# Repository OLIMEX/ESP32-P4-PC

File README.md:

# ESP32-P4-PC
ESP32-P4 all in one computer with x4 USB hosts Audio, HDMI, MIPI CSI, MIPI DSI, LiPo battery operation, Ethernet with POE

https://www.olimex.com/Products/IoT/ESP32-P4/ESP32-P4-PC/open-source-hardware

## Licensee
* Hardware is released under CERN Open Hardware Licence Version 2 - Strongly Reciprocal
* Software is released under MIT Licensee
* Documentation is released under CC BY-SA 4.0

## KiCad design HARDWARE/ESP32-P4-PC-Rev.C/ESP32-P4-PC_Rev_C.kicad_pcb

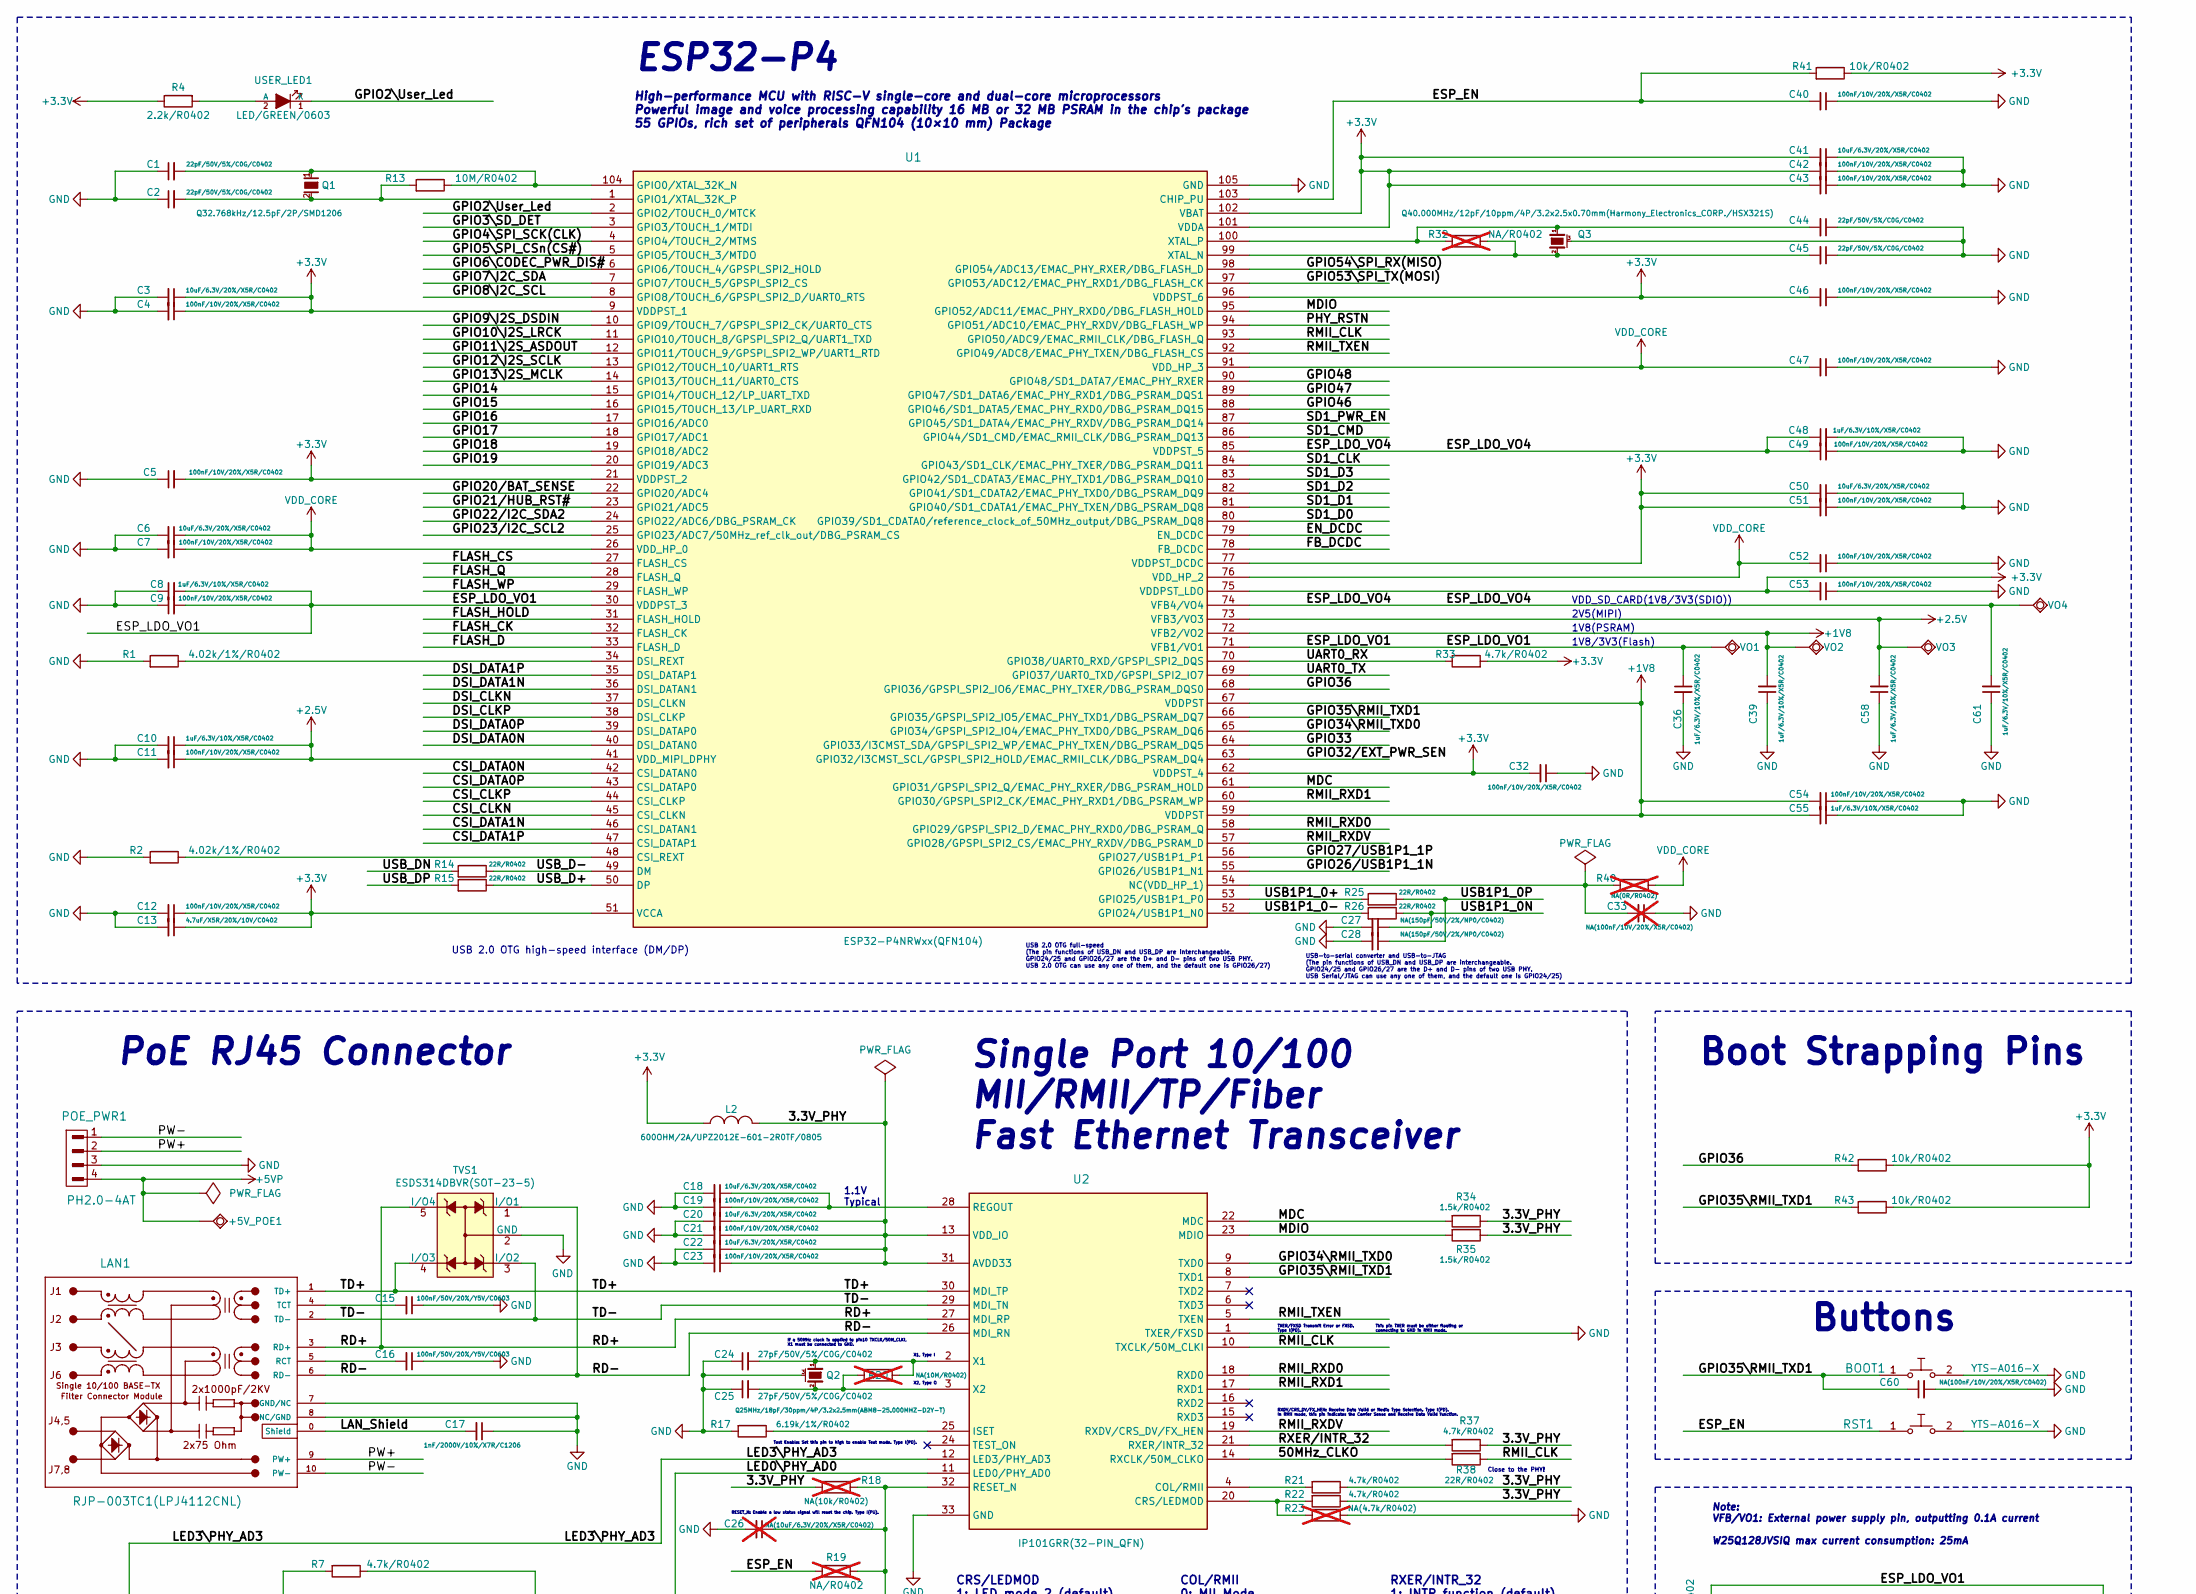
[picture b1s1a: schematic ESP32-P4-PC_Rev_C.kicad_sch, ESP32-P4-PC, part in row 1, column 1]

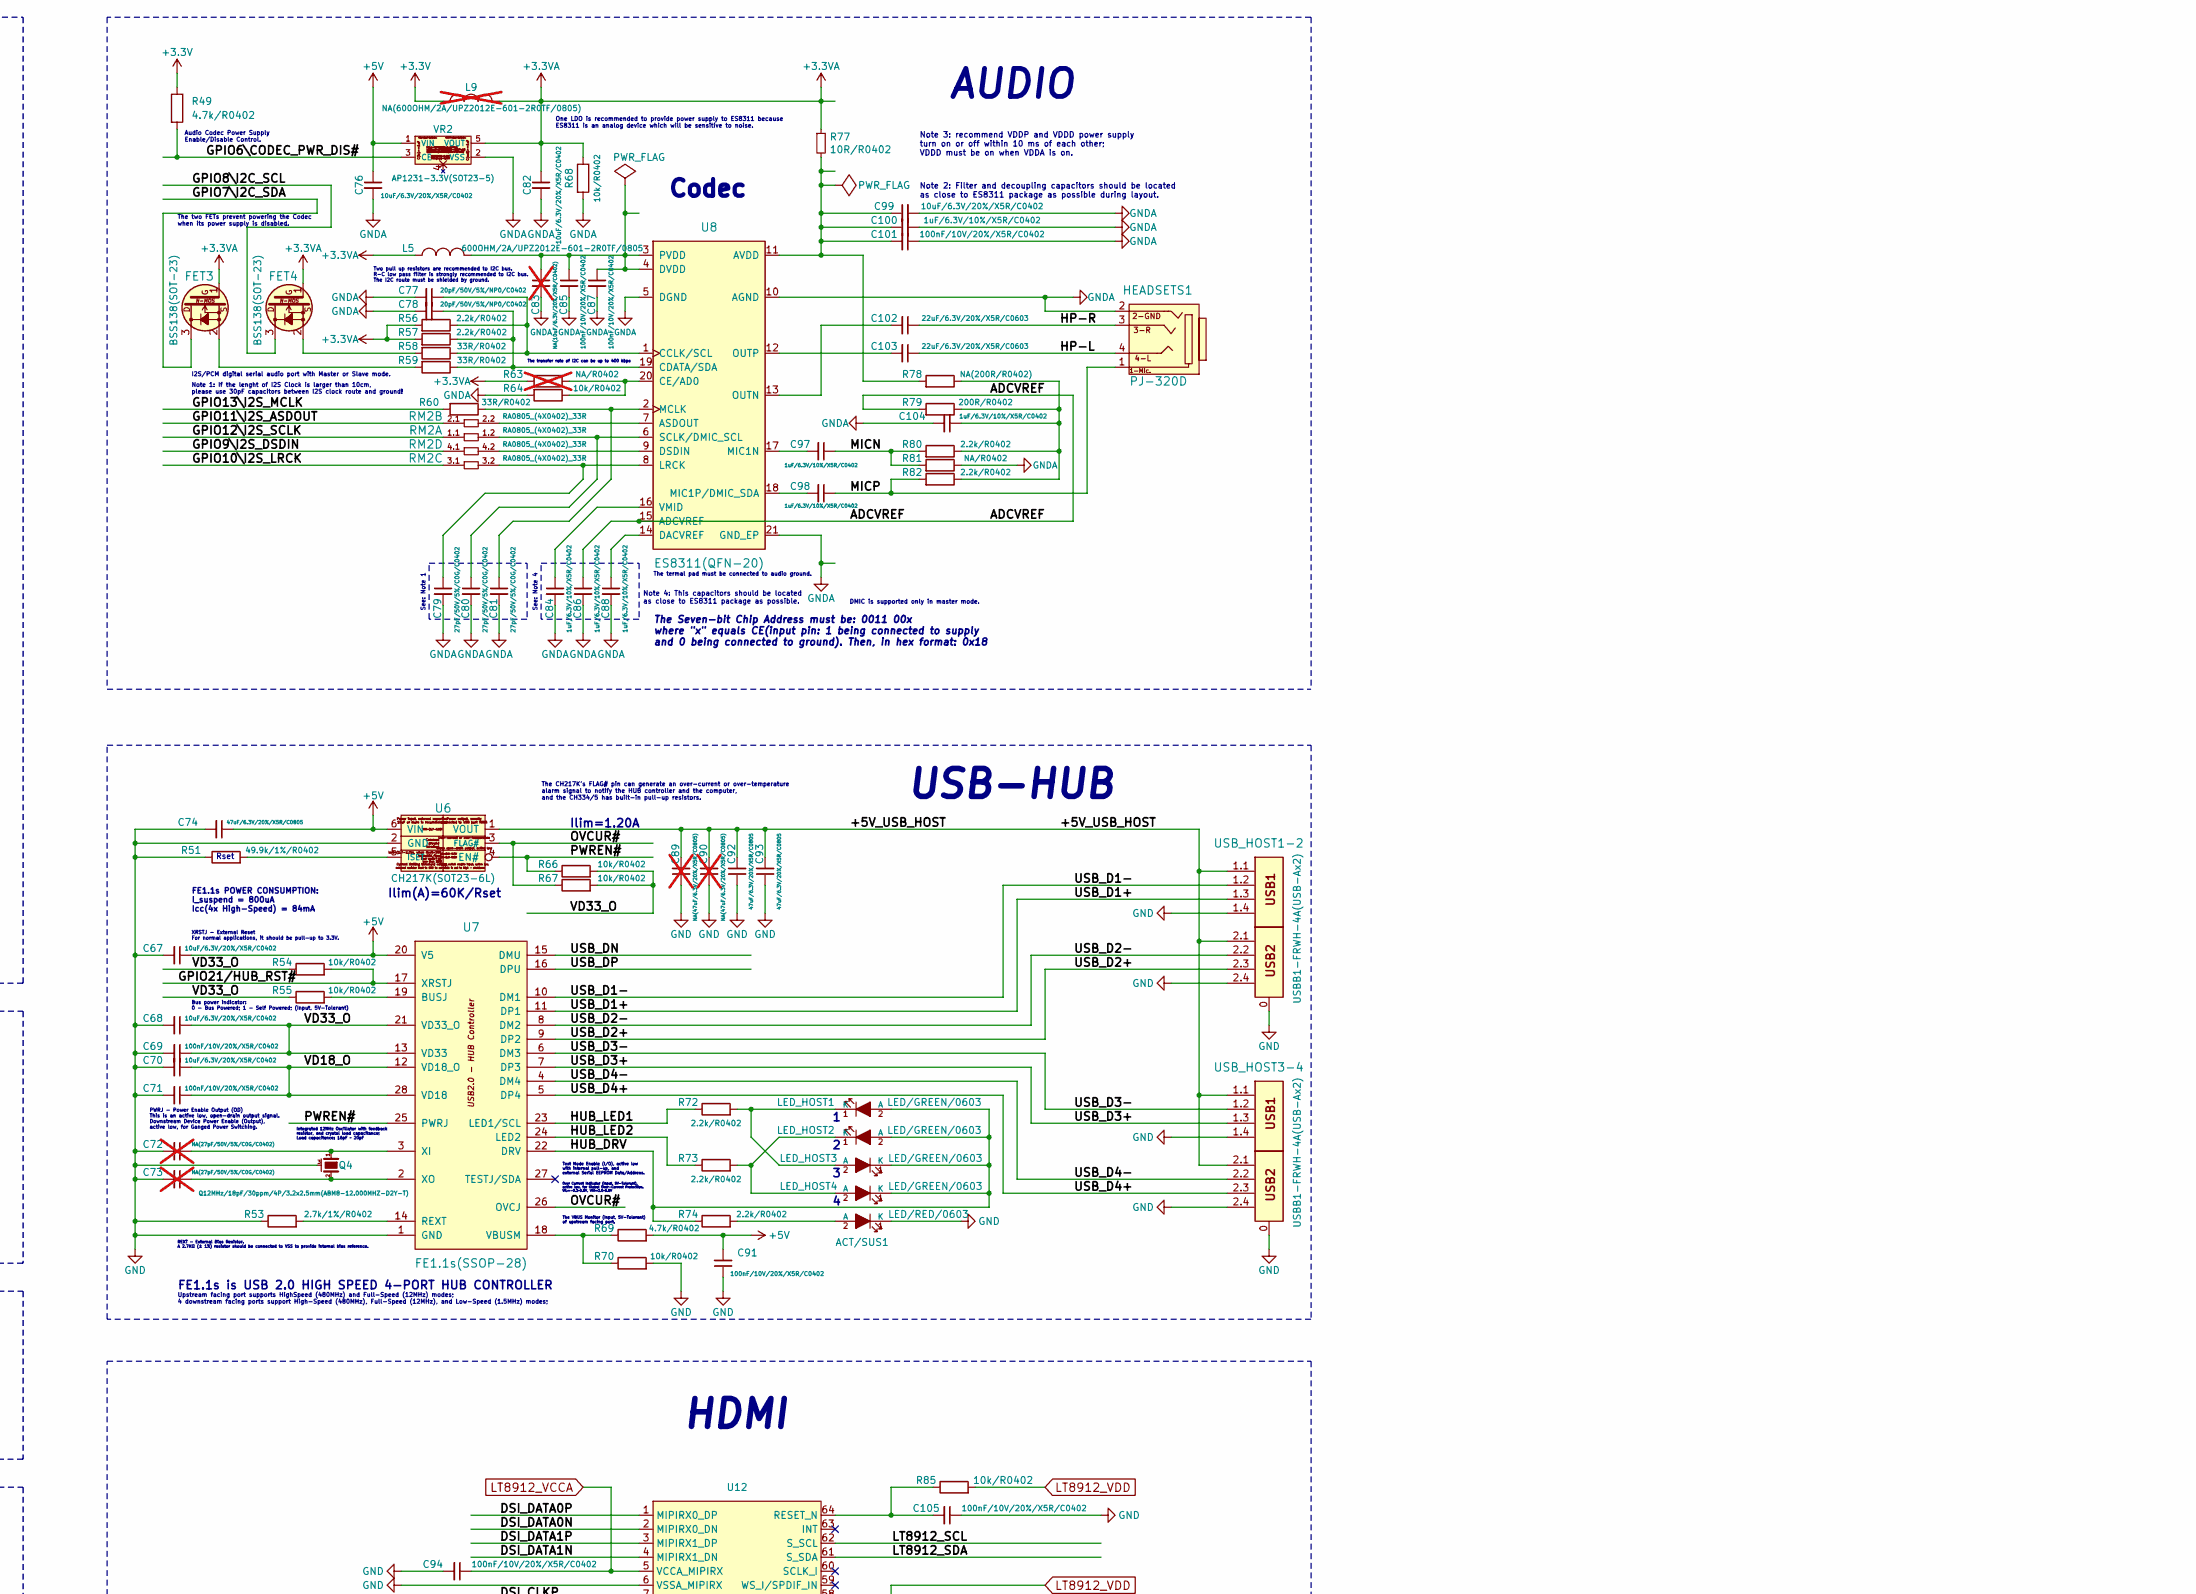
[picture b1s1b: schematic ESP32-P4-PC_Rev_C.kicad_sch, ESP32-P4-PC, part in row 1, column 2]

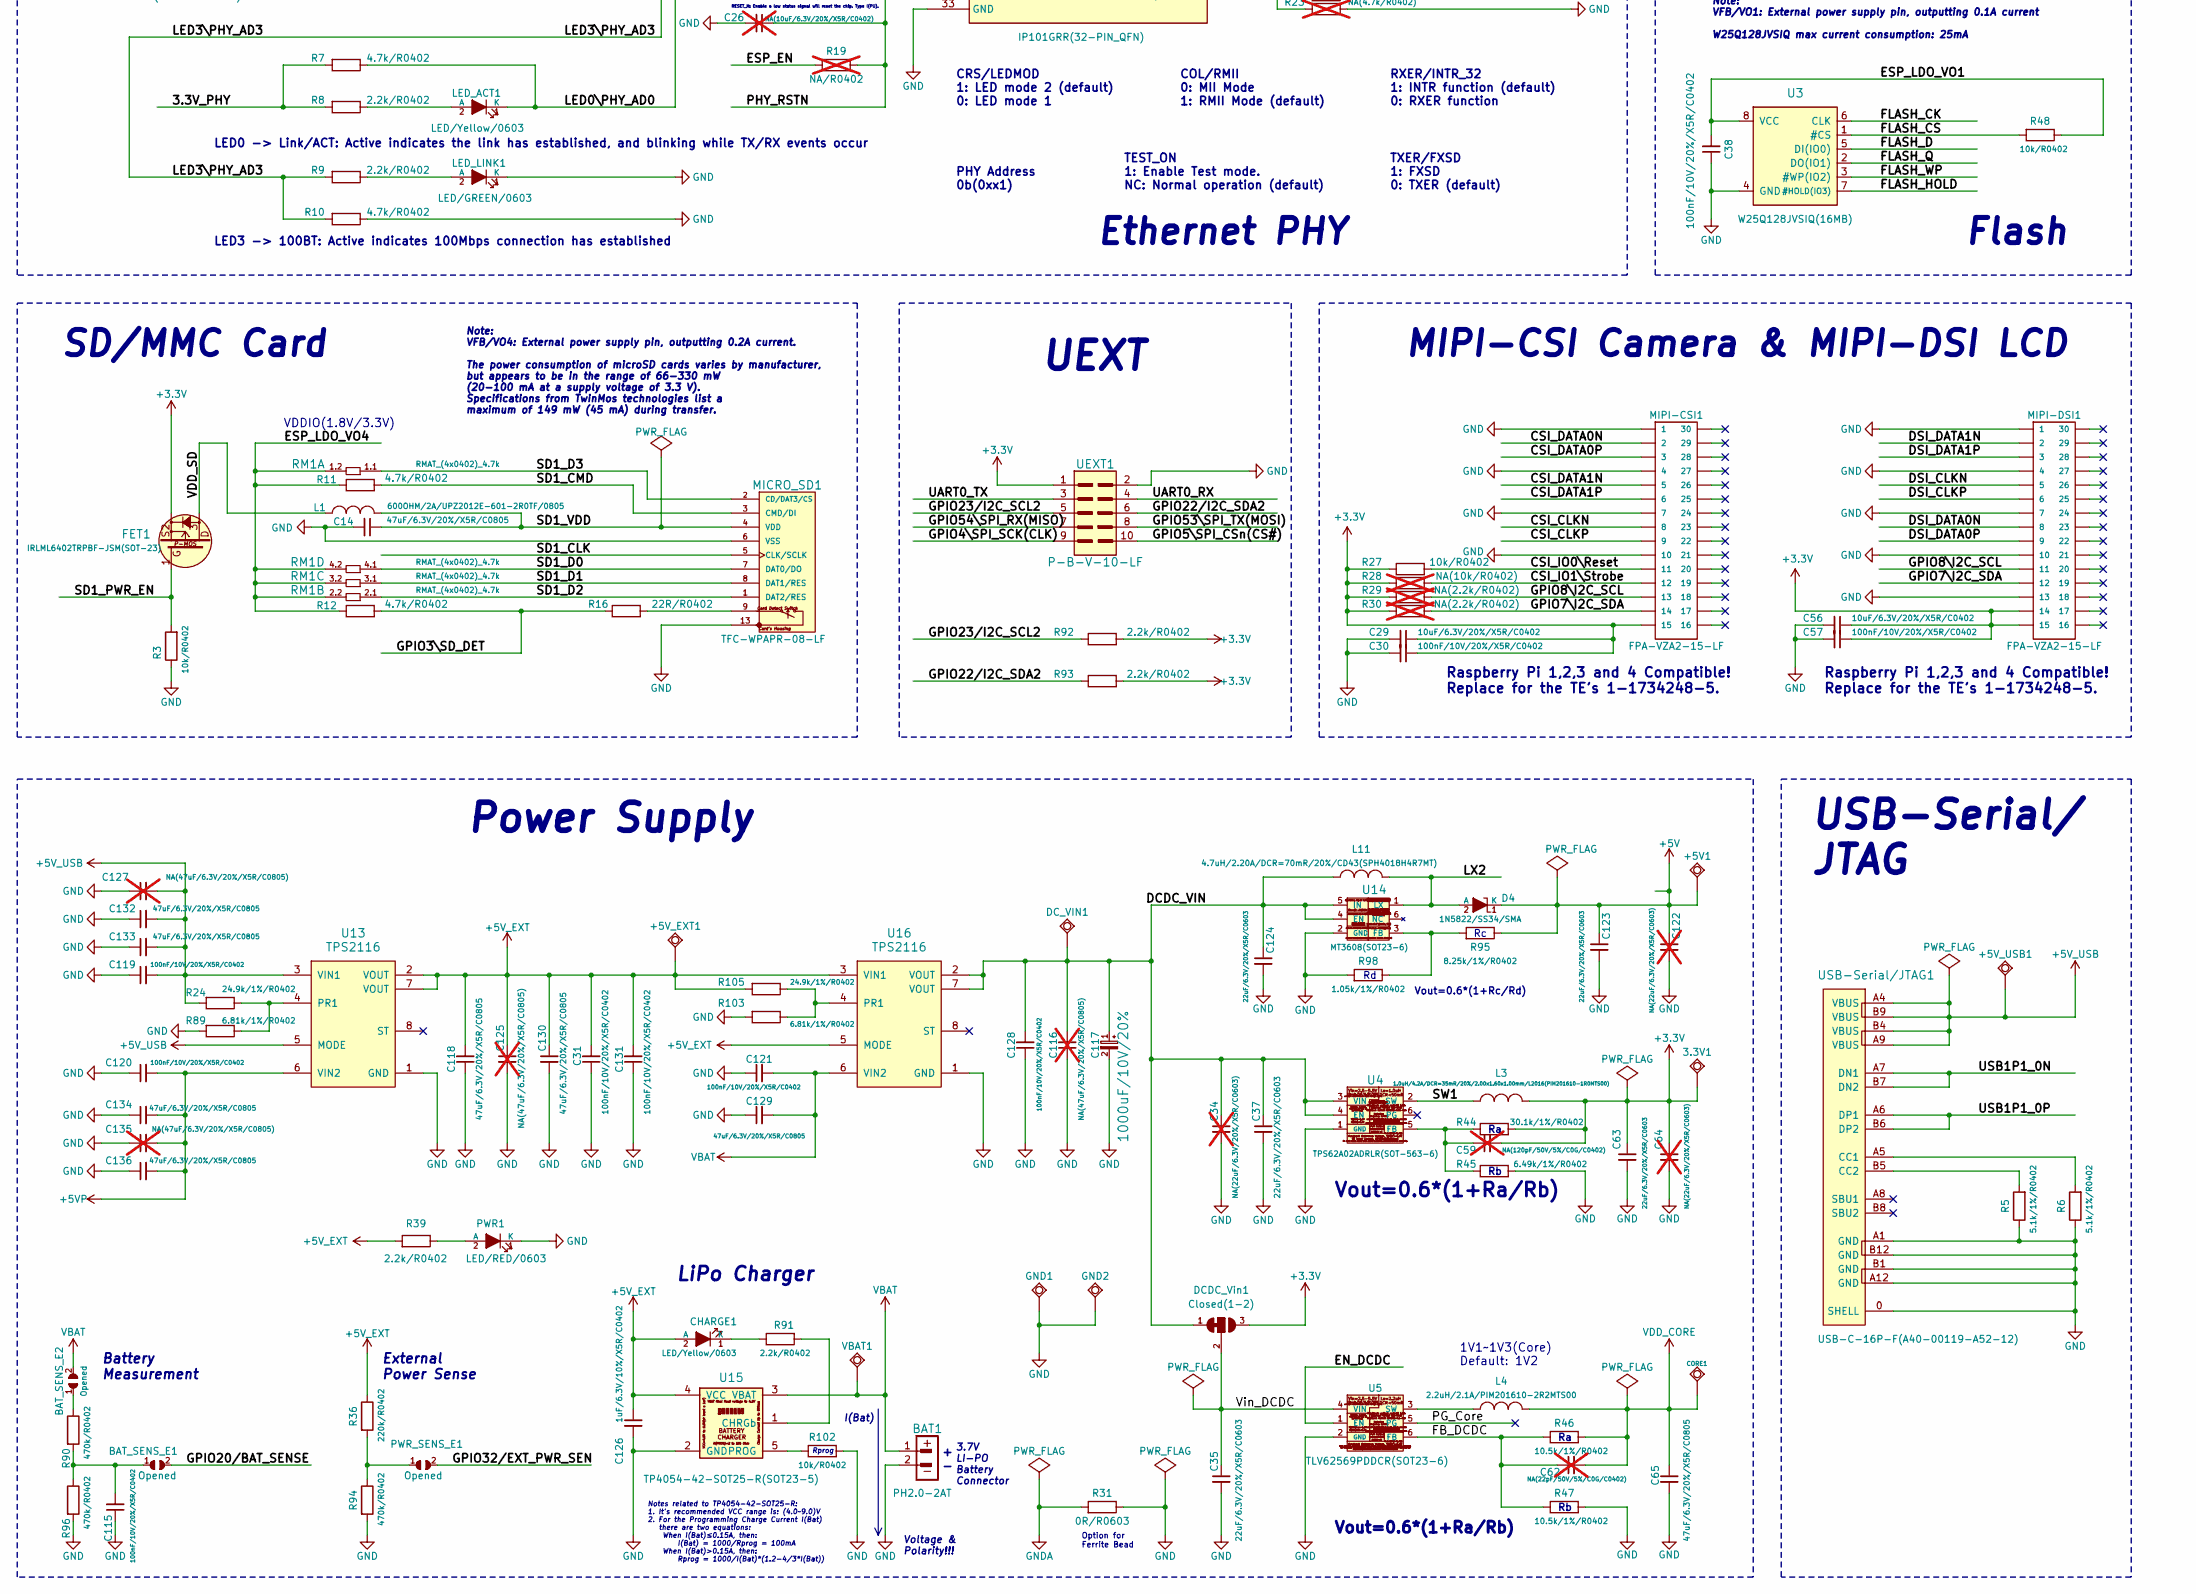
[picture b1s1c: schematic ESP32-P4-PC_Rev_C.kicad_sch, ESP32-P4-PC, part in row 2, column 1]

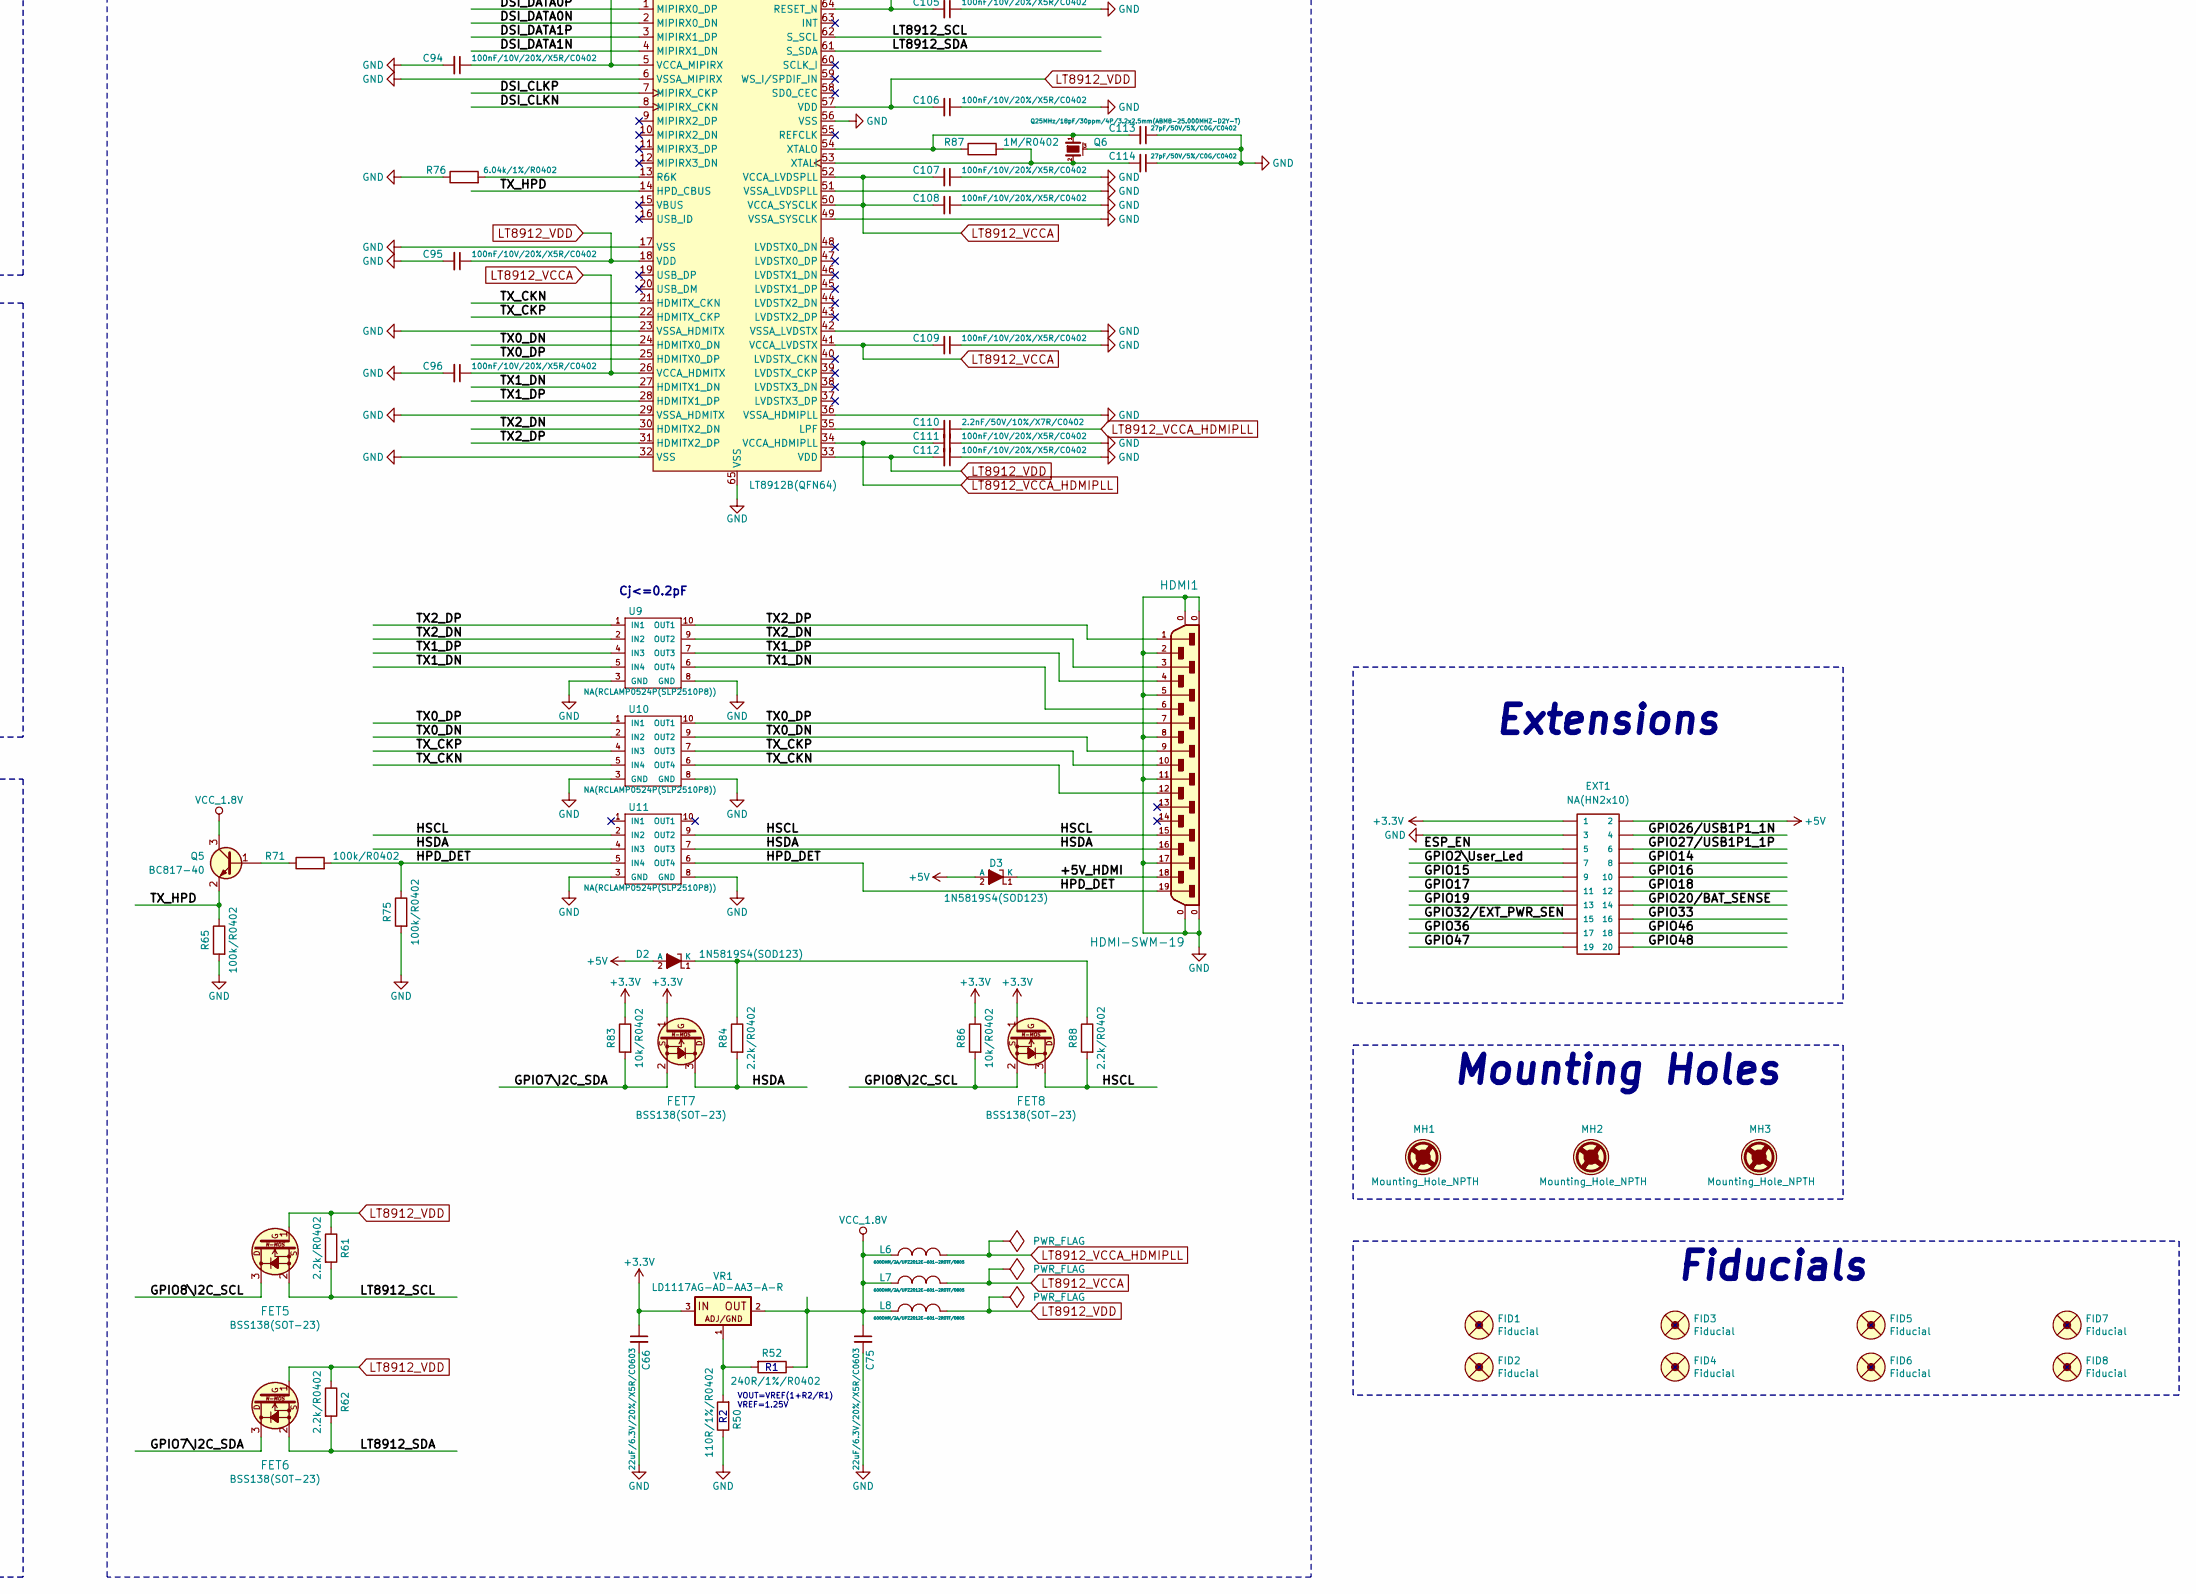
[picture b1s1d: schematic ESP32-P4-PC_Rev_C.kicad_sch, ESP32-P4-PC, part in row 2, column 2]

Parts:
3.3V1: TESTPAD; TESTPAD_40-ROUND
+5V1, +5V_EXT1, +5V_POE1, +5V_USB1: TESTPAD; TESTPAD_40-ROUND
ACT/SUS1: LED/RED/0603; LED_0603_KA
BAT1: PH2.0-2AT; PH2.0-2AT(BAT)
BAT_SENS_E1, BAT_SENS_E2: Opened; SJ_1_SMALLER
BOOT1: YTS-A016-X
C1, C2, C44, C45: 22pF/50V/5%/C0G/C0402; C_0402_5MIL_DWS
C3, C6, C18, C20, C22, C29, C41, C50, C56, C67, C68, C70, C76, C82, C99: 10uF/6.3V/20%/X5R/C0402; C_0402_5MIL_DWS
C4, C5, C7, C9, C11, C12, C19, C21, C23, C30, C31, C32, C38, C40, C42, C43, C46, C47, C49, C51, C52, C53, C54, C57, C69, C71, C85, C87, C91, C94, C95, C96, C101, C105, C106, C107, C108, C109, C111, C112, C115, C119, C120, C121, C128, C131: 100nF/10V/20%/X5R/C0402; C_0402_5MIL_DWS
C8, C10, C36, C39, C48, C55, C58, C61, C84, C86, C88, C97, C98, C100, C104, C126: 1uF/6.3V/10%/X5R/C0402; C_0402_5MIL_DWS
C13: 4.7uF/X5R/20%/10V/C0402; C_0402_5MIL_DWS
C14, C65, C74, C92, C93, C118, C129, C130, C132, C133, C134, C136: 47uF/6.3V/20%/X5R/C0805; C_0805_5MIL_DWS
C15, C16: 100nF/50V/20%/Y5V/C0603; C_0603_5MIL_DWS
C17: 1nF/2000V/10%/X7R/C1206; C_1206_5MIL_DWS_ISO
C24, C25, C79, C80, C81, C113, C114: 27pF/50V/5%/C0G/C0402; C_0402_5MIL_DWS
C26, C83: NA(10uF/6.3V/20%/X5R/C0402); C_0402_5MIL_DWS; not fitted
C27, C28: NA(150pF/50V/2%/NP0/C0402); C_0402_5MIL_DWS
C33: NA(100nF/10V/20%/X5R/C0402); C_0402_5MIL_DWS; not fitted
C34, C64, C122: NA(22uF/6.3V/20%/X5R/C0603); C_0603_5MIL_DWS; not fitted
C35, C37, C63, C66, C75, C102, C103, C123, C124: 22uF/6.3V/20%/X5R/C0603; C_0603_5MIL_DWS
C59: NA(120pF/50V/5%/C0G/C0402); C_0402_5MIL_DWS; not fitted
C60: NA(100nF/10V/20%/X5R/C0402); C_0402_5MIL_DWS
C62: NA(22pF/50V/5%/C0G/C0402); C_0402_5MIL_DWS; not fitted
C72, C73: NA(27pF/50V/5%/C0G/C0402); C_0402_5MIL_DWS; not fitted
C77, C78: 20pF/50V/5%/NP0/C0402; C_0402_5MIL_DWS
C89, C90, C116, C125, C127, C135: NA(47uF/6.3V/20%/X5R/C0805); C_0805_5MIL_DWS; not fitted
C110: 2.2nF/50V/10%/X7R/C0402; C_0402_5MIL_DWS
C117: 1000uF/10V/20%; CPOL-RM3.5mm_8.0x11.5mm_PTH
CHARGE1: LED/Yellow/0603; LED_0603_KA
CORE1: TESTPAD; TESTPAD_40-ROUND
D2, D3: 1N5819S4(SOD123); SOD-123_1C-2A_KA
D4: 1N5822/SS34/SMA; SMA-KA
DCDC_Vin1: Closed(1-2); SJ_2_SMALL_12_TIED
DC_VIN1: TESTPAD; TESTPAD_40-ROUND
EXT1: NA(HN2x10); HN2x10
FET1: IRLML6402TRPBF-JSM(SOT-23); SOT23
FET3, FET4, FET5, FET6, FET7, FET8: BSS138(SOT-23); SOT23
FID1, FID3, FID5, FID7: Fiducial; Fiducial1x3
FID2, FID4, FID6, FID8: Fiducial; Fiducial1x3_Paste
GND1, GND2: TESTPAD; TESTPAD_40-ROUND
HDMI1: HDMI-SWM-19; HDMI-SWM-19_Paste
HEADSETS1: PJ-320D
L1, L2, L5, L6, L7, L8: 600OHM/2A/UPZ2012E-601-2R0TF/0805; L_0805_5MIL_DWS
L3: 1.0uH/4.2A/DCR=35mR/20%/2.00x1.60x1.00mm/L2016(PI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; L_2016_MM
L4: 2.2uH/2.1A/PIM201610-2R2MTS00; L_2016_MM
L9: NA(600OHM/2A/UPZ2012E-601-2R0TF/0805); L_0805_5MIL_DWS; not fitted
L11: 4.7uH/2.20A/DCR=70mR/20%/CD43(SPH4018H4R7MT); CD42(43)
LAN1: RJP-003TC1(LPJ4112CNL)
LED_ACT1: LED/Yellow/0603; LED_0603_KA
LED_HOST1, LED_HOST2, LED_HOST3, LED_HOST4: LED/GREEN/0603; LED_0603_KA
LED_LINK1: LED/GREEN/0603; LED_0603_KA
MH1, MH2, MH3: Mounting_Hole_NPTH; Mounting_Hole_Drill-3.3mm_Clerance-7mm
MICRO_SD1: TFC-WPAPR-08-LF; TFC-WPAPR-08
MIPI-CSI1: FPA-VZA2-15-LF; TE_1-1734248-5
MIPI-DSI1: FPA-VZA2-15-LF; TE_1-1734248-5
POE_PWR1: PH2.0-4AT; PH2.0-4PLB
PWR1: LED/RED/0603; LED_0603_KA
PWR_SENS_E1: Opened; SJ_1_SMALLER
Q1: Q32.768kHz/12.5pF/2P/SMD1206; CM7V-T1A(Crystal_Package-1206_3.20x1.50x0.65mm)
Q2, Q6: Q25MHz/18pF/30ppm/4P/3.2x2.5mm(ABM8-25.000MHZ-D2Y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; TSX-3.2x2.5mm_GND(3)
Q3: Q40.000MHz/12pF/10ppm/4P/3.2x2.5x0.70mm(Harmony_E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; TSX-3.2x2.5mm_GND(3)
Q4: Q12MHz/18pF/30ppm/4P/3.2x2.5mm(ABM8-12.000MHZ-D2Y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; TSX-3.2x2.5mm_GND(3)
Q5: BC817-40; SOT23
R1, R2: 4.02k/1%/R0402; R_0402_5MIL_DWS
R3, R27, R41, R42, R43, R48, R54, R55, R64, R66, R67, R68, R70, R83, R85, R86, R102: 10k/R0402; R_0402_5MIL_DWS
R4, R8, R9, R39, R56, R57, R61, R62, R72, R73, R74, R80, R82, R84, R88, R91, R92, R93: 2.2k/R0402; R_0402_5MIL_DWS
R5, R6: 5.1k/1%/R0402; R_0402_5MIL_DWS
R7, R10, R11, R12, R21, R22, R33, R37, R49, R69: 4.7k/R0402; R_0402_5MIL_DWS
R13: 10M/R0402; R_0402_5MIL_DWS
R14, R15, R16, R25, R26, R38: 22R/R0402; R_0402_5MIL_DWS
R17: 6.19k/1%/R0402; R_0402_5MIL_DWS
R18, R28: NA(10k/R0402); R_0402_5MIL_DWS; not fitted
R19, R32, R63: NA/R0402; R_0402_5MIL_DWS; not fitted
R20: NA(10M/R0402); R_0402_5MIL_DWS; not fitted
R23: NA(4.7k/R0402); R_0402_5MIL_DWS; not fitted
R24, R105: 24.9k/1%/R0402; R_0402_5MIL_DWS
R29, R30: NA(2.2k/R0402); R_0402_5MIL_DWS; not fitted
R31: 0R/R0603; R_0603_5MIL_DWS
R34, R35: 1.5k/R0402; R_0402_5MIL_DWS
R36: 220k/R0402; R_0402_5MIL_DWS
R40: NA(0R/R0402); R_0402_5MIL_DWS; not fitted
R44: 30.1k/1%/R0402; R_0402_5MIL_DWS
R45: 6.49k/1%/R0402; R_0402_5MIL_DWS
R46, R47: 10.5k/1%/R0402; R_0402_5MIL_DWS
R50: 110R/1%/R0402; R_0402_5MIL_DWS
R51: 49.9k/1%/R0402; R_0402_5MIL_DWS
R52: 240R/1%/R0402; R_0402_5MIL_DWS
R53: 2.7k/1%/R0402; R_0402_5MIL_DWS
R58, R59, R60: 33R/R0402; R_0402_5MIL_DWS
R65, R71, R75: 100k/R0402; R_0402_5MIL_DWS
R76: 6.04k/1%/R0402; R_0402_5MIL_DWS
R77: 10R/R0402; R_0402_5MIL_DWS
R78: NA(200R/R0402); R_0402_5MIL_DWS
R79: 200R/R0402; R_0402_5MIL_DWS
R81: NA/R0402; R_0402_5MIL_DWS
R87: 1M/R0402; R_0402_5MIL_DWS
R89, R103: 6.81k/1%/R0402; R_0402_5MIL_DWS
R90, R94, R96: 470k/R0402; R_0402_5MIL_DWS
R95: 8.25k/1%/R0402; R_0402_5MIL_DWS
R98: 1.05k/1%/R0402; R_0402_5MIL_DWS
RM1: RMAT_(4x0402)_4.7k; RA0805_(4X0402)_xx_BIGGEROUTPADS
RM2: RA0805_(4X0402)_33R; RA0805_(4X0402)_xx_BIGGEROUTPADS
RST1: YTS-A016-X
TVS1: ESDS314DBVR(SOT-23-5); SOT-23-5
U1: ESP32-P4NRWxx(QFN104); QFN104_10mm×10mm_Pitch_0.35mm
U2: IP101GRR(32-PIN_QFN); QFN32_EP(33)_4.00x4.00x0.80mm_Pitch_0.40mm
U3: W25Q128JVSIQ(16MB); SO-8_208mil
U4: TPS62A02ADRLR(SOT-563-6); SOT-563-6
U5: TLV62569PDDCR(SOT23-6); SOT23-6
U6: CH217K(SOT23-6L); SOT23-6
U7: FE1.1s(SSOP-28); SSOP28_10x4mm_Pitch_0.64mm
U8: ES8311(QFN-20); QFN-20_EP(21)_3x3x0.6mm_Pitch_0.4mm
U9, U10, U11: NA(RCLAMP0524P(SLP2510P8)); SLP2510P8_TEST
U12: LT8912B(QFN64); QFN64_7.5x7.5mm_Pitch_0.4mm
U13, U16: TPS2116; SOT-5X3
U14: MT3608(SOT23-6); SOT23-6
U15: TP4054-42-SOT25-R(SOT23-5); SOT-23-5
UEXT1: P-B-V-10-LF; GBH-254-SMT-10
USB-Serial/JTAG1: USB-C-16P-F(A40-00119-A52-12); USB2.0_TYPE-C(A40-00119-A52-12)_Paste
USB_HOST1-2, USB_HOST3-4: USBB1-FRWH-4A(USB-Ax2); USB_TWO_LEVEL
USER_LED1: LED/GREEN/0603; LED_0603_KA
VBAT1: TESTPAD; TESTPAD_40-ROUND
VO1, VO2, VO3, VO4: TESTPAD; TESTPAD_40-ROUND
VR1: LD1117AG-AD-AA3-A-R; SOT223
VR2: AP1231-3.3V(SOT23-5); SOT-23-5

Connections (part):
+1V8: C39.2, C54.2, C55.2, U1.59 (VDDPST), U1.67 (VDDPST), U1.72 (VFB2/VO2), VO2.1 (Pad)
+2.5V: C10.1, C11.1, C58.2, U1.41 (VDD_MIPI_DPHY), U1.73 (VFB3/VO3), VO3.1 (Pad)
+3.3V: 3.3V1.1 (Pad), C3.1, C4.1, C5.2, C12.1, C13.1, C29.1, C30.1, C32.2, C41.2, C42.2, C43.2, C46.2, C50.2, C51.2, C53.2, C56.1, C57.1, C59.2, C63.1, C64.1, C66.1, DCDC_Vin1.3, EXT1.1, FET1.2, FET7.1 (G), FET8.1 (G), L2.1, L3.2, L9.1, MIPI-CSI1.15, MIPI-DSI1.14, MIPI-DSI1.15, R4.1, R27.1, R28.1, R29.1, R30.1, R33.2, R41.1, R42.1, R43.1, R44.2, R49.1, R83.1, R86.1, R92.2, R93.2, U1.9 (VDDPST_1), U1.21 (VDDPST_2), U1.51 (VCCA), U1.62 (VDDPST_4), U1.75 (VDDPST_LDO), U1.77 (VDDPST_DCDC), U1.96 (VDDPST_6), U1.101 (VDDA), U1.102 (VBAT), UEXT1.1, VR1.3 (IN)
+3.3VA: C82.1, FET3.1 (G), FET4.1 (G), L5.1, L9.2, R56.2, R57.2, R63.2, R68.1, R77.1, VR2.5 (VOUT)
+5V: +5V1.1 (Pad), C67.1, C74.1, C76.1, C91.2, C122.1, C123.1, D2.2 (A), D3.2 (A), D4.1 (K), EXT1.2, R69.2, R95.1, U6.6 (VIN), U7.20 (V5), VR2.1 (VIN)
+5VP: +5V_POE1.1 (Pad), C120.2, C134.2, C135.2, C136.2, POE_PWR1.4, U13.6 (VIN2)
+5V_EXT: +5V_EXT1.1 (Pad), C31.2, C118.2, C125.1, C126.1, C130.1, C131.2, CHARGE1.2 (A), R36.1, R39.2, R105.2, U13.2 (VOUT), U13.7 (VOUT), U15.4 (VCC), U16.3 (VIN1), U16.5 (MODE)
+5V_USB: +5V_USB1.1 (Pad), C119.2, C127.2, C132.2, C133.2, R24.2, U13.3 (VIN1), U13.5 (MODE), USB-Serial/JTAG1.A4 (VBUS), USB-Serial/JTAG1.A9 (VBUS), USB-Serial/JTAG1.B4 (VBUS), USB-Serial/JTAG1.B9 (VBUS)
/3.3V_PHY: C20.1, C21.1, C22.1, C23.1, L2.2, R7.2, R8.2, R18.1, R21.1, R22.1, R34.1, R35.1, R37.1, U2.13 (VDD_IO), U2.31 (AVDD33)
/50MHz_CLKO: R38.2, U2.14 (RXCLK/50M_CLKO)
/+5V_HDMI: D3.1 (K), HDMI1.18
/+5V_USB_HOST: C89.2, C90.2, C92.2, C93.2, U6.1 (VOUT), USB_HOST1-2.1.1, USB_HOST1-2.2.1, USB_HOST3-4.1.1, USB_HOST3-4.2.1
/ADCVREF: C86.1, R79.2, U8.15 (ADCVREF)
/CSI_CLKN: MIPI-CSI1.8, U1.45 (CSI_CLKN)
/CSI_CLKP: MIPI-CSI1.9, U1.44 (CSI_CLKP)
/CSI_DATA0N: MIPI-CSI1.2, U1.42 (CSI_DATAN0)
/CSI_DATA0P: MIPI-CSI1.3, U1.43 (CSI_DATAP0)
/CSI_DATA1N: MIPI-CSI1.5, U1.46 (CSI_DATAN1)
/CSI_DATA1P: MIPI-CSI1.6, U1.47 (CSI_DATAP1)
/CSI_IO0\Reset: MIPI-CSI1.11, R27.2
/CSI_IO1\Strobe: MIPI-CSI1.12, R28.2
/DCDC_VIN: C34.1, C37.1, C116.2, C117.1 (+), C124.1, C128.2, DCDC_Vin1.1, DC_VIN1.1 (Pad), L11.2, U4.3 (VIN), U4.4 (EN), U14.4 (EN), U14.5 (IN), U16.2 (VOUT), U16.7 (VOUT)
/DSI_CLKN: MIPI-DSI1.5, U1.37 (DSI_CLKN), U12.8 (MIPIRX_CKN)
/DSI_CLKP: MIPI-DSI1.6, U1.38 (DSI_CLKP), U12.7 (MIPIRX_CKP)
/DSI_DATA0N: MIPI-DSI1.8, U1.40 (DSI_DATAN0), U12.2 (MIPIRX0_DN)
/DSI_DATA0P: MIPI-DSI1.9, U1.39 (DSI_DATAP0), U12.1 (MIPIRX0_DP)
/DSI_DATA1N: MIPI-DSI1.2, U1.36 (DSI_DATAN1), U12.4 (MIPIRX1_DN)
/DSI_DATA1P: MIPI-DSI1.3, U1.35 (DSI_DATAP1), U12.3 (MIPIRX1_DP)
/EN_DCDC: U1.79 (EN_DCDC), U5.1 (EN)
/ESP_EN: C40.2, EXT1.5, R19.1, R41.2, RST1.1, U1.103 (CHIP_PU)
/ESP_LDO_VO1: C8.2, C9.2, C36.1, C38.2, R48.1, U1.30 (VDDPST_3), U1.71 (VFB1/VO1), U3.8 (VCC), VO1.1 (Pad)
/ESP_LDO_VO4: C48.1, C49.1, C61.2, R11.1, R12.1, RM1.1.2, RM1.2.2, RM1.3.2, RM1.4.2, U1.74 (VFB4/VO4), U1.85 (VDDPST_5), VO4.1 (Pad)
/FB_DCDC: C62.1, R46.1, R47.1, U1.78 (FB_DCDC), U5.6 (FB)
/FLASH_CK: U1.32 (FLASH_CK), U3.6 (CLK)
/FLASH_CS: R48.2, U1.27 (FLASH_CS), U3.1 (#CS)
/FLASH_D: U1.33 (FLASH_D), U3.5 (DI(IO0))
/FLASH_HOLD: U1.31 (FLASH_HOLD), U3.7 (#HOLD(IO3))
/FLASH_Q: U1.28 (FLASH_Q), U3.2 (DO(IO1))
/FLASH_WP: U1.29 (FLASH_WP), U3.3 (#WP(IO2))
/GPIO2\User_Led: EXT1.7, U1.2 (GPIO2/TOUCH_0/MTCK), USER_LED1.1 (K)
/GPIO3\SD_DET: R12.2, R16.1, U1.3 (GPIO3/TOUCH_1/MTDI)
/GPIO4\SPI_SCK(CLK): U1.4 (GPIO4/TOUCH_2/MTMS), UEXT1.9
/GPIO5\SPI_CSn(CS#): U1.5 (GPIO5/TOUCH_3/MTDO), UEXT1.10
/GPIO6\CODEC_PWR_DIS#: R49.2, U1.6 (GPIO6/TOUCH_4/GPSPI_SPI2_HOLD), VR2.3 (CE)
/GPIO7\I2C_SDA: FET3.3 (D), FET6.3 (D), FET7.2 (S), MIPI-CSI1.14, MIPI-DSI1.12, R30.2, R83.2, U1.7 (GPIO7/TOUCH_5/GPSPI_SPI2_CS)
/GPIO8\I2C_SCL: FET4.3 (D), FET5.3 (D), FET8.2 (S), MIPI-CSI1.13, MIPI-DSI1.11, R29.2, R86.2, U1.8 (GPIO8/TOUCH_6/GPSPI_SPI2_D/UART0_RTS)
/GPIO9\I2S_DSDIN: RM2.4.1, U1.10 (GPIO9/TOUCH_7/GPSPI_SPI2_CK/UART0_CTS)
/GPIO10\I2S_LRCK: RM2.3.1, U1.11 (GPIO10/TOUCH_8/GPSPI_SPI2_Q/UART1_TXD)
/GPIO11\I2S_ASDOUT: RM2.2.1, U1.12 (GPIO11/TOUCH_9/GPSPI_SPI2_WP/UART1_RTD)
/GPIO12\I2S_SCLK: RM2.1.1, U1.13 (GPIO12/TOUCH_10/UART1_RTS)
/GPIO13\I2S_MCLK: R60.2, U1.14 (GPIO13/TOUCH_11/UART0_CTS)
/GPIO14: EXT1.8, U1.15 (GPIO14/TOUCH_12/LP_UART_TXD)
/GPIO15: EXT1.9, U1.16 (GPIO15/TOUCH_13/LP_UART_RXD)
/GPIO16: EXT1.10, U1.17 (GPIO16/ADC0)
/GPIO17: EXT1.11, U1.18 (GPIO17/ADC1)
/GPIO18: EXT1.12, U1.19 (GPIO18/ADC2)
/GPIO19: EXT1.13, U1.20 (GPIO19/ADC3)
/GPIO20/BAT_SENSE: BAT_SENS_E1.2, EXT1.14, U1.22 (GPIO20/ADC4)
/GPIO21/HUB_RST#: R54.2, U1.23 (GPIO21/ADC5), U7.17 (XRSTJ)
/GPIO22/I2C_SDA2: R93.1, U1.24 (GPIO22/ADC6/DBG_PSRAM_CK), UEXT1.6
/GPIO23/I2C_SCL2: R92.1, U1.25 (GPIO23/ADC7/50MHz_ref_clk_out/DBG_PSRAM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), UEXT1.5
/GPIO26/USB1P1_1N: EXT1.4, U1.55 (GPIO26/USB1P1_N1)
/GPIO27/USB1P1_1P: EXT1.6, U1.56 (GPIO27/USB1P1_P1)
/GPIO32/EXT_PWR_SEN: EXT1.15, PWR_SENS_E1.2, U1.63 (GPIO32/I3CMST_SCL/GPSPI_SPI2_HOLD/EMAC_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)
/GPIO33: EXT1.16, U1.64 (GPIO33/I3CMST_SDA/GPSPI_SPI2_WP/EMAC_PH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)
/GPIO34\RMII_TXD0: U1.65 (GPIO34/GPSPI_SPI2_IO4/EMAC_PHY_TXD0/DBG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), U2.9 (TXD0)
/GPIO35\RMII_TXD1: BOOT1.1, C60.1, R43.2, U1.66 (GPIO35/GPSPI_SPI2_IO5/EMAC_PHY_TXD1/DBG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), U2.8 (TXD1)
/GPIO36: EXT1.17, R42.2, U1.68 (GPIO36/GPSPI_SPI2_IO6/EMAC_PHY_TXER/DBG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)
/GPIO46: EXT1.18, U1.88 (GPIO46/SD1_DATA5/EMAC_PHY_RXD0/DBG_PSRA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)
/GPIO47: EXT1.19, U1.89 (GPIO47/SD1_DATA6/EMAC_PHY_RXD1/DBG_PSRA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)
/GPIO48: EXT1.20, U1.90 (GPIO48/SD1_DATA7/EMAC_PHY_RXER)
/GPIO53\SPI_TX(MOSI): U1.97 (GPIO53/ADC12/EMAC_PHY_RXD1/DBG_FLASH_CK), UEXT1.8
/GPIO54\SPI_RX(MISO): U1.98 (GPIO54/ADC13/EMAC_PHY_RXER/DBG_FLASH_D), UEXT1.7
/HP-L: C103.1, HEADSETS1.4
/HP-R: C102.1, HEADSETS1.3
/HPD_DET: HDMI1.19, R71.2, R75.1, U11.5 (IN4), U11.6 (OUT4)
/HSCL: FET8.3 (D), HDMI1.15, R88.2, U11.2 (IN2), U11.9 (OUT2)
/HSDA: FET7.3 (D), HDMI1.16, R84.2, U11.4 (IN3), U11.7 (OUT3)
/HUB_DRV: LED_HOST1.2 (A), LED_HOST2.2 (A), LED_HOST3.1 (K), LED_HOST4.1 (K), R74.1, U7.22 (DRV)
/HUB_LED1: R72.1, U7.23 (LED1/SCL)
/HUB_LED2: R73.1, U7.24 (LED2)
/LAN_Shield: C17.2, LAN1.0 (Shield)
/LED0\PHY_AD0: LED_ACT1.1 (K), R7.1, U2.11 (LED0/PHY_AD0)
/LED3\PHY_AD3: R9.2, R10.2, U2.12 (LED3/PHY_AD3)
/LT8912_SCL: FET5.2 (S), R61.2, U12.62 (S_SCL)
/LT8912_SDA: FET6.2 (S), R62.2, U12.61 (S_SDA)
/LX2: D4.2 (A), L11.1, U14.1 (LX)
/MDC: R34.2, U1.61 (GPIO31/GPSPI_SPI2_Q/EMAC_PHY_RXER/DBG_P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), U2.22 (MDC)
/MDIO: R35.2, U1.95 (GPIO52/ADC11/EMAC_PHY_RXD0/DBG_FLASH_HO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), U2.23 (MDIO)
/MICN: C97.1, R80.2, R81.2
/MICP: C98.1, HEADSETS1.1, R82.2
/OVCUR#: R67.1, U6.3 (FLAG#), U7.26 (OVCJ)
/PG_Core: U5.5 (PG)
/PHY_RSTN: C26.1, R18.2, R19.2, U1.94 (GPIO51/ADC10/EMAC_PHY_RXDV/DBG_FLASH_WP), U2.32 (RESET_N)
/PW+: LAN1.9 (PW+), POE_PWR1.2
/PW-: LAN1.10 (PW-), POE_PWR1.1
/PWREN#: R66.1, U6.4 (EN#), U7.25 (PWRJ)
/RD+: LAN1.3 (RD+), TVS1.5 (I/O4), U2.27 (MDI_RP)
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
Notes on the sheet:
One LDO is recommended to provide power supply to ES8311 because ES8311 is an analog device which will be sensitive to noise.
Cj<=0.2pF
XRSTJ - External Reset For normal applications, it should be pull-up to 3.3V.
Note: VFB/VO1: External power supply pin, outputting 0.1A current W25Q128JVSIQ max current consumption: 25mA
TXER/FXSD Transmit Error or FXSD. Type I(PD).
USB-to-serial converter and USB-to-JTAG (The pin functions of USB_DN and USB_DP are interchangeable. GPIO24/25 and GPIO26/27 are the D+ and D- pins of two USB PHY. USB Serial/JTAG can use any one of them, and the default one is GPIO24/25)
Power Supply
Ilim=1.20A
The termal pad must be connected to audio ground.
Vout=0.6*(1+Ra/Rb)
Two pull up resistors are recommended to I2C bus. R-C low pass filter is strongly recommended to I2C bus. The I2C route must be shielded by ground.
I2S/PCM digital serial audio port with Master or Slave mode.
The two FETs prevent powering the Codec when its power supply is disabled.
Note 4: This capacitors should be located as close to ES8311 package as possible.
REXT - External Bias Resistor. A 2.7KΩ (± 1%) resistor should be connected to VSS to provide internal bias reference.
See: Note 1
Boot Strapping Pins
Mounting Holes
LED0 -> Link/ACT: Active indicates the link has established, and blinking while TX/RX events occur
Over Current Indicator (Input, 5V-Tolerant), active low, for Global Over-Current Protection. VIL=-0.3~0.8V, VIH=2.0~5.5V
RXER/INTR_32 1: INTR function (default) 0: RXER function
COL/RMII 0: MII Mode 1: RMII Mode (default)
This pin TXER must be either floating or connecting to GND in RMII mode.
The transfer rate of I2C can be up to 400 kbps
RXDV/CRS_DV/FX_HEN: Receive Data Valid or Media Type Selection. Type I(PD). In RMII mode, this pin indicates the Carrier Sense and Receive Data Valid function.
TXER/FXSD 1: FXSD 0: TXER (default)
3.7V LI-PO Battery Connector
FE1.1s is USB 2.0 HIGH SPEED 4-PORT HUB CONTROLLER
TEST_ON 1: Enable Test mode. NC: Normal operation (default)
Ethernet PHY
The CH217K's FLAG# pin can generate an over-current or over-temperature alarm signal to notify the HUB controller and the computer, and the CH334/5 has built-in pull-up resistors.
LiPo Charger
See: Note 4
Test Mode Enable (I/O), active low with internal pull-up, and external Serial EEPROM Data/Address.
Test Enable: Set this pin to high to enable Test mode. Type I(PD).
High-performance MCU with RISC-V single-core and dual-core microprocessors Powerful image and voice processing capability 16 MB or 32 MB PSRAM in the chip's package 55 GPIOs, rich set of peripherals QFN104 (10×10 mm) Package
USB 2.0 OTG high-speed interface (DM/DP)
AUDIO
If a 50MHz clock is applied to pin10 TXCLK/50M_CLKI, X1 must be connected to GND.
1V8/3V3(Flash)

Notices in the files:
HARDWARE/ESP32-P4-PC-Rev.C/ESP32-P4-PC_Rev_C.kicad_pcb:
(C) 2026
